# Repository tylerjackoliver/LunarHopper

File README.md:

# Lunar Hopper GitHub Repo

This is the repo for the Lunar Hopper on-board computer and control system.

## Test script usage
Tester file format:
*time (seconds) | command | arguments*

Tester file example:
```
0 start high
0.01 gyro 1 2
0.05 accel 1 2 3
0.1 throttle 50
0.27 press 90
1 abort high
5 disarm high
10 end
```

Test file example output:
```
-0.08030: ACT_PIN_X_POS reads 0
-0.08025: ACT_PIN_X_NEG reads 0
-0.08022: ACT_PIN_Y_POS reads 0
-0.06462: ACT_PIN_Y_NEG reads 0
-0.06457: SOL_PIN_VENT reads 0
-0.03106: SOL_PIN_PRES reads 0
-0.03098: SOL_PIN_OX reads 0
0.000371: 0 start high
0.012370: 0.01 gyro 1 2
0.085079: 0.05 accel 1 2 3
0.108033: 0.1 throttle 50
0.326400: 0.27 press 90
1.030022: 1 abort high
5.057830: 5 disarm high
10.06733: 10 end
10.10730: Test has concluded
```

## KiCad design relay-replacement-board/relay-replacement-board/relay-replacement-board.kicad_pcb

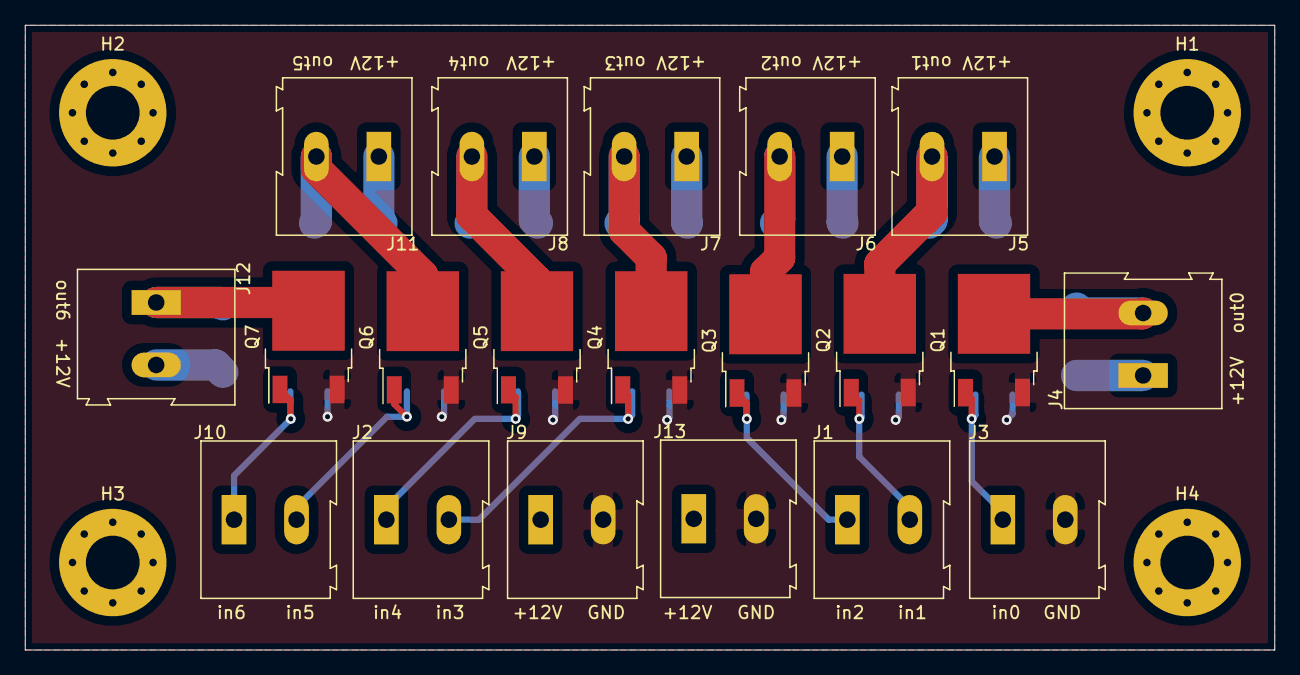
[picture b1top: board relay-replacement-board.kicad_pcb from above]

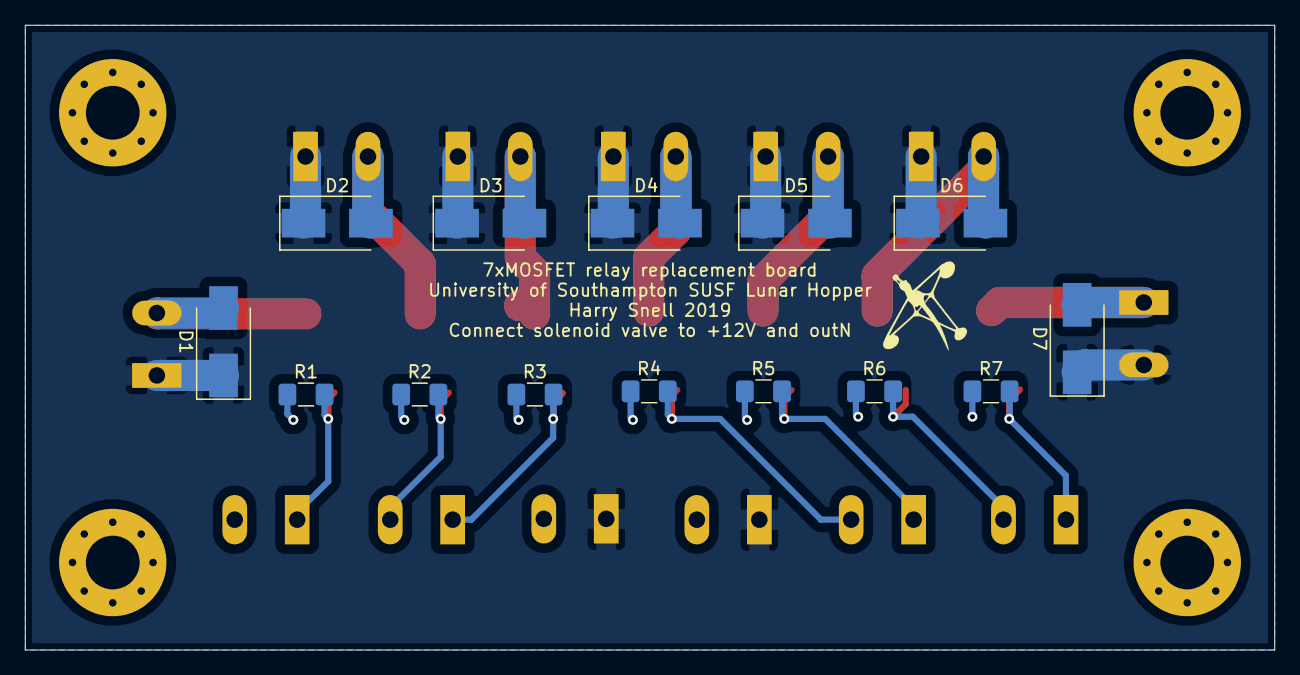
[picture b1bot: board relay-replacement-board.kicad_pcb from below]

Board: 2 copper layers, 100.0 x 50.0 mm, 38 parts (14 on the bottom side), 16 nets.

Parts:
D1, D2, D3, D4, D5, D6, D7: D; D_SMB_Handsoldering
H1, H2, H3, H4: MountingHole_4.3mm_M4_Pad_Via
J1, J2, J3, J4, J5, J6, J7, J8, J9, J10, J11, J12, J13: Conn_01x02; TerminalBlock_Altech_AK300-2_P5.00mm
Q1, Q2, Q3, Q4, Q5, Q6, Q7: NVD5865NL; TO-252-2
R1, R2, R3, R4, R5, R6, R7: 10K; R_1206_3216Metric_Pad1.42x1.75mm_HandSolder

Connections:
+12V: D1.1, D2.1, D3.1, D4.1, D5.1, D6.1, D7.1, J4.1, J5.1, J6.1, J7.1, J8.1, J9.1, J11.1, J12.2, J13.1
/trigger0: J3.1, Q1.1, R1.2
/trigger1: J1.2, Q2.1, R2.2
/trigger2: J1.1, Q3.1, R3.2
/trigger3: J2.2, Q4.1, R4.2
/trigger4: J2.1, Q5.1, R5.2
/trigger5: J10.2, Q6.1, R6.2
/trigger6: J10.1, Q7.1, R7.2
GND: J3.2, J9.2, J13.2, Q1.3, Q2.3, Q3.3, Q4.3, Q5.3, Q6.3, Q7.3, R1.1, R2.1, R3.1, R4.1, R5.1, R6.1, R7.1
unnamed: D1.2, J4.2, Q1.2
unnamed: D2.2, J5.2, Q2.2
unnamed: D3.2, J6.2, Q3.2
unnamed: D4.2, J7.2, Q4.2
unnamed: D5.2, J8.2, Q5.2
unnamed: D6.2, J11.2, Q6.2
unnamed: D7.2, J12.1, Q7.2

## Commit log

2016-10-27 Added main computation script
2016-10-27 Added main computation file
2016-10-28 Added working ox_pulse() function
2016-10-28 Refactored ledpinN => ACS(direction) for readability
2016-10-29 Added note in HopperControl.c
2016-10-30 need to change the un-named pins when we know what they do
2016-10-31 Unnamed pins are for testing purposes
    renaming these pins shouldn't be necessary
2016-10-31 Adjusts serial behaviour in HopperControl.c
2016-11-01 Removes unnecessary pin references in HopperControl.c
2016-11-01 Removed duplicate command variable in HopperControl.c
2016-11-02 Adds notes to ACS_Check() in HopperControl.c
2016-11-06 Removes unnecessary functions in HopperControl.c
2018-02-28 Change non-standard "boolean" to standard "bool"
2018-02-28 Change to const pin declarations and rename accordingly
    Following standard ALL_CAPS for names of constants.
    Names are created for pins first by description, then pin, followed by
    identifier (eg. SOL_PIN_VENT) where descriptions are:
    ACCEL - accelerometer
    ACT - attitude control thruster
    GYRO - gyroscope
2018-02-28 Remove instances of ? operator
    Improves readiability of the code for anyone not well versed in C.
2018-02-28 Remove wasDisarmed variable in disarm()
    wasDisarmed was declared, and set either true or false, but not used in
    disarm() (the only scope in which it existed).
2018-02-28 Create constant state integers for status variables
    Statuses were recorded and modified throughout
    as 0, 1, or 2, corresponding to OFF, ON, or TEST. Creating constants allows setting
    to STATUS_OFF anywhere in program, improving readability of code and
    removing need for redundant "record as OFF" comments.
2018-02-28 Resolve inconsistencies with vent statuses in disarm()
    Previously the two vent statuses were coded as OFF, but commented as ON.
    Entirely on assumption, I've turned both vents on, as opening vents
    when trying to disarm, or passivate a system, seems like a good idea.
2018-02-28 Remove artefacts created by 93d92122b5abb6e02135833c41db1a76506ebe45
2018-02-28 Create constants for valve HIGH/LOW toggles
    Aptly named VALVE_ON and VALVE_OFF for lots of swish readability
2018-02-28 Resolve inconsistencies with valve statuses in disarm()
    Follow on of 987777d10436639d3124edaab32d6d8bb942d07a
    Another hunch, I think we want the vent valve open, to relieve pressure in
    fuel feed system.
    Assuming, just based on my previous status reasoning, that we want
    passivation of the entire system, therefore we want to vent pressure in
    the ACS as well. However, the big issue here is that the only way to
2018-03-01 Implement calculation of current pressure
    The existing calculation return 1 to 40 bar, the new
    one correctly returns 0 to 40 bar.
    Calculation also implemented in function so that it
    can be called from anywhere in the program without
    doing so explicity (previous method).
2018-03-01 Fix countless general things
    Checked and created all constants that were constant and renamed them
    to match style.
    Moved global variable into local variables where possible.
    Identified occurences of all variables and marked with !!! for future removal.
    Made copious stylistic changes to be more consistent throughout.
2018-03-07 Create merged_lunar_hopper_code
    Merged Shane's functions with main loop code.
    I left out the calibration in the main loop as I'm assuming it's going to be used with a gyroscope so it will only need to be calibrated once which I have put in the setup().
2018-03-10 Change const/variable conflicitons
    Fixes tylerjackoliver/LunarHopper#15 and fixes tylerjackoliver/LunarHopper#16
    which were introduced in d3b16f3f5c604a4446ee814e90f2580a178c306b
2018-03-10 Create .gitignore
    So I can work entirely in Visual Studio Code and work on creating a seamless,
    consistent environment for everyone.
2018-03-10 Create files
2018-03-10 Reorganize directories so Arduino will run test .ino file
2018-03-10 Implement basic wrapping
    This is by no means perfect, optimized, or even looks good,
    but as a proof of concept, it functions.
2018-03-10 Add code for testing using Receiver
2018-03-10 Remove junk serial outputs used for debug
    Also stop transmit successful packet being sent by receipt of packet by receiver.
2018-03-20 Change accel and gyro references to get data from MPU
    There are a couple things that could be modified/made more robust, for
    example the ACCEL_SENSITIVITY and GYRO_SENSITIVITY constants are
    hardcoded, yet it is possbile to read what these values are set to from
    the MPU itself, so if it is configured differently, the sensitivity can
    adapt dynamically.
    This code compiles, and in theory it runs, however it has had issues
2018-03-20 Create test file for experimenting with MPU
2018-03-20 Add fun little function initializing 4 ACS "thrusters"
2018-03-21 Remove unused variable and incorrect comments
2018-06-22 Create and implement Telemetry library
2018-11-01 Change something
    Frankly, I don't recall why.. Bad me.
2018-11-06 Code restructuring
    Removed legacy code.
    Moved some declerations to within functions.
    Applied a consistent camelCase convention to declarations, can change to _ if prefered.
    Minor optimisations.
2018-11-20 Update #2
    Code looks complete just needs testing
2019-01-29 Improving Variable Consistency
2019-02-05 Remove duplicaed code
2019-10-22 Create Tester.py
    Test script for a pi to interface with the arduino. Specific DAC controll to be implemented.
2019-10-22 Updated README and added functionality
    Can now read custom files names and the output file is in a more legible format.
2019-11-23 Create eCAD files for relay replacement files
2019-11-23 Placement of components on board
2019-11-23 Trace routing
2019-11-23 M4 mounting holes
2019-11-23 added extra +12V in
    The rated current on the terminal blocks is 16A each which is less than the possible current draw if every valve were on at the same time. This change increases the current capacity to and from the +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
2019-11-23 Minor adjustments to trace routing
2019-11-23 routing changes
2019-11-23 Added flyback diodes
    These protect the MOSFETs when they switch off. PCB also reorganised and shrunk slightly to 10*5cm
2019-11-23 Added M4 mounting holes
    THese are not currently connected to Ground but could be
2019-11-24 Added silkscreen
    Text explaining what to connect where on the board
2019-11-24 remove bak files
2019-11-24 change silkscreen orientation
2019-11-29 Added team logo to back silkscreen
2019-11-29 Gerber file export
    exported Gerber files as required by Elecrow for manufacturing
2019-11-29 Final exit
2019-11-29 zipped files for upload
